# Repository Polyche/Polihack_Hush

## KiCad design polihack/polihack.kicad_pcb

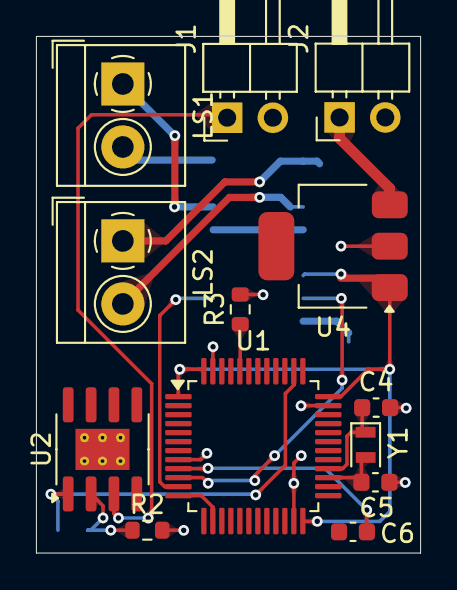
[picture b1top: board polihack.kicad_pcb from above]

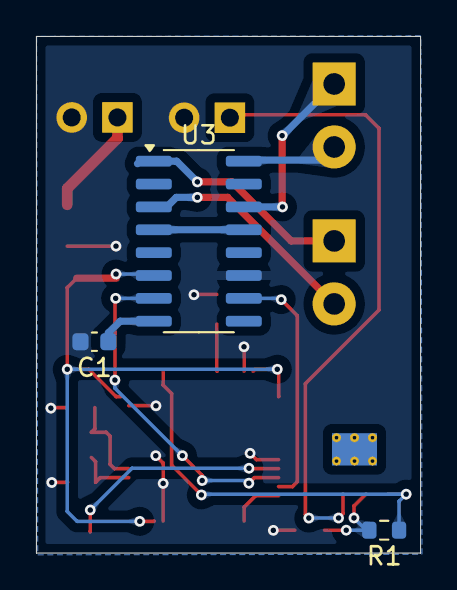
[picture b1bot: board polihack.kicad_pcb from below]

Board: 2 copper layers, 21.3 x 28.7 mm, 16 parts (3 on the bottom side), 17 nets.

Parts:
C1: 1uF; C_0603_1608Metric
C4, C5: 22uF; C_0603_1608Metric
C6: 100nF; C_0603_1608Metric
J1: Microphone connector; PinHeader_1x02_P2.54mm_Horizontal
J2: Battery; PinHeader_1x02_P2.54mm_Horizontal
LS1, LS2: Speaker; TerminalBlock_4Ucon_1x02_P3.50mm_Horizontal
R1, R2, R3: 10k; R_0603_1608Metric
U1: STM32F103C8Tx; LQFP-48_7x7mm_P0.5mm
U2: TL072; SOIC-8-1EP_3.9x4.9mm_P1.27mm_EP2.29x3mm_ThermalVias
U3: PAM8403D; SOP-16_3.9x9.9mm_P1.27mm
U4: LM78L05_TO92; SOT-223
Y1: Crystal; Crystal_SMD_2012-2Pin_2.0x1.2mm

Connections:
5V: C6.1, U1.1 (VBAT), U1.24 (VDD), U1.36 (VDD), U1.48 (VDD), U3.4 (PVDD), U3.5 (~MUTE), U3.6 (VDD), U3.13 (PVDD), U4.1 (VO)
GND: C1.2, C4.2, C5.1, J1.2, J2.2, R2.2, R3.2, U1.8 (VSSA), U1.23 (VSS), U1.35 (VSS), U1.47 (VSS), U3.11 (GND), U4.2 (GND)
unnamed: J1.1, U2.3 (+)
unnamed: J2.1, U4.3 (VI)
unnamed: R3.1, U1.44 (BOOT0)
unnamed: U1.10 (PA0), U3.7 (INL)
unnamed: U1.11 (PA1), U3.10 (INR)
unnamed: R1.1, U1.38 (PA15), U2.1
unnamed: C5.2, U1.27 (PB14), Y1.2
unnamed: C4.1, U1.28 (PB15), Y1.1
unnamed: C6.2, U1.9 (VDDA)
unnamed: R1.2, R2.1, U2.2 (-)
unnamed: LS2.1, U3.1 (LOUT+)
unnamed: LS2.2, U3.3 (LOUT-)
unnamed: LS1.2, U3.16 (ROUT+)
unnamed: LS1.1, U3.14 (ROUT-)
unnamed: C1.1, U3.8 (VREF)

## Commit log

2025-03-01 Polihack_Project
2025-03-01 Presentation
